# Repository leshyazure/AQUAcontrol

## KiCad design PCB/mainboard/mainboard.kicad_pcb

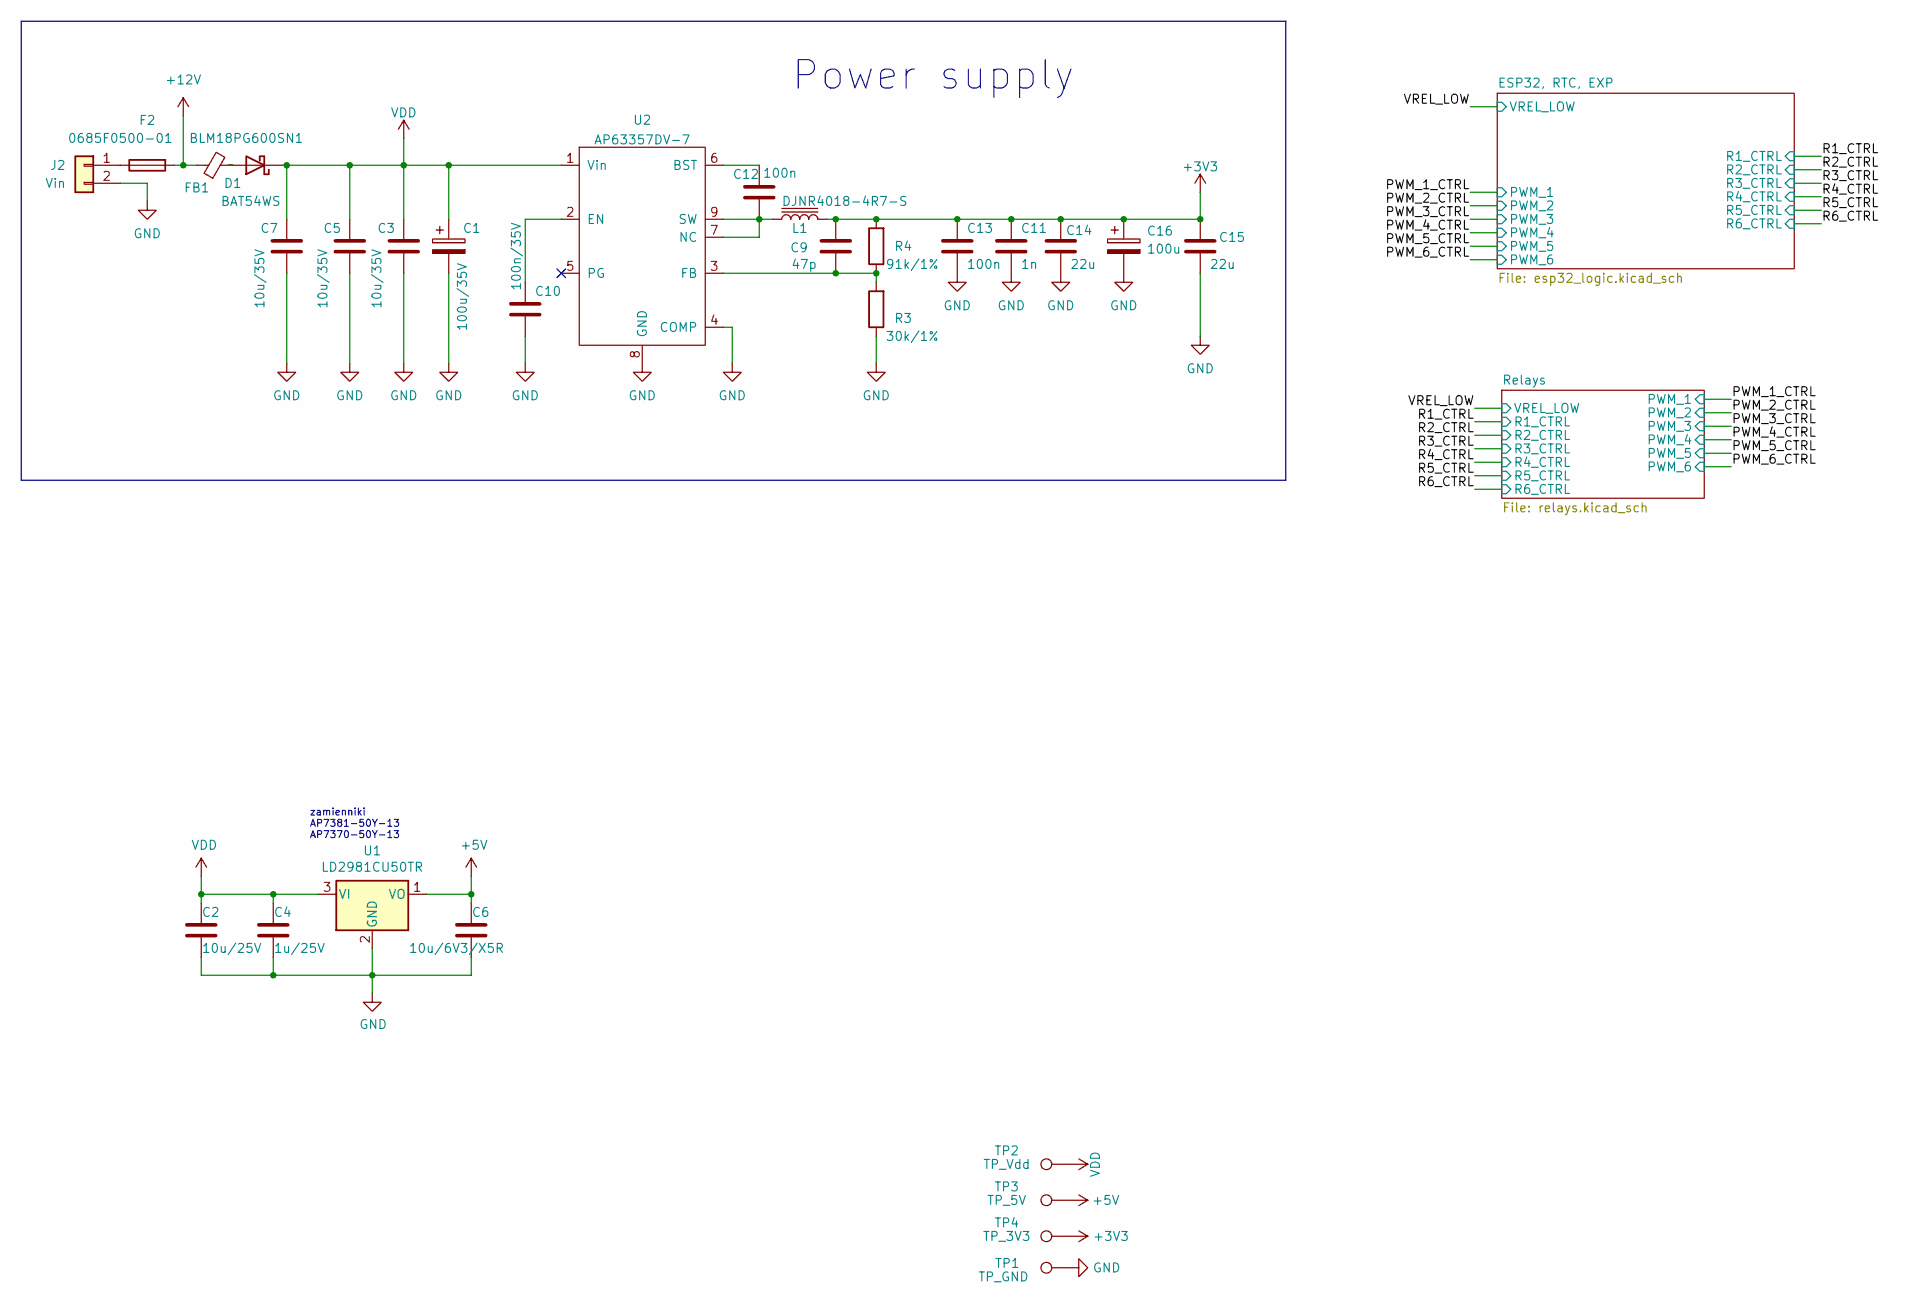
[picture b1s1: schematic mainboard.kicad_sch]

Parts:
C1: 100u/35V; CP_Elec_6.3x5.4
C2: 10u/25V; C_0805_2012Metric
C3, C5, C7: 10u/35V; C_1206_3216Metric
C4: 1u/25V; C_0603_1608Metric
C6: 10u/6V3/X5R; C_0603_1608Metric
C9: 47p; C_0603_1608Metric
C10: 100n/35V; C_0603_1608Metric
C11: 1n; C_0603_1608Metric
C12, C13: 100n; C_0603_1608Metric
C14, C15: 22u; C_0805_2012Metric
C16: 100u; CP_Elec_6.3x5.4
D1: BAT54WS; SOT-23
F2: 0685F0500-01; Fuse_1206_3216Metric
FB1: BLM18PG600SN1; L_0603_1608Metric
J2: Vin; PhoenixContact_MSTBA_2,5_2-G-5,08_1x02_P5.08mm_Horizontal
L1: DJNR4018-4R7-S; L_Bourns-SRN4018
R3: 30k/1%; R_0603_1608Metric_Pad0.98x0.95mm_HandSolder
R4: 91k/1%; R_0603_1608Metric_Pad0.98x0.95mm_HandSolder
TP1: TP_GND; TestPoint_THTPad_D1.0mm_Drill0.5mm
TP2: TP_Vdd; TestPoint_THTPad_D1.0mm_Drill0.5mm
TP3: TP_5V; TestPoint_THTPad_D1.0mm_Drill0.5mm
TP4: TP_3V3; TestPoint_THTPad_D1.0mm_Drill0.5mm
U1: LD2981CU50TR; SOT-89-3
U2: AP63357DV-7; V-DFN3020-13_Type_A_grid_stencil

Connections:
+3V3: C9.1, C11.1, C13.1, C14.1, C15.1, C16.1, L1.2, R4.2, TP4.1; also elsewhere on the board
+5V: C6.1, TP3.1, U1.1 (VO); also elsewhere on the board
+12V: F2.2, FB1.1; also elsewhere on the board
GND: C1.2, C2.2, C3.2, C4.2, C5.2, C6.2, C7.2, C10.2, C11.2, C13.2, C14.2, C15.2, C16.2, J2.2, R3.1, TP1.1, U1.2 (GND), U2.4 (COMP), U2.8 (GND); also elsewhere on the board
unnamed: C9.2, R3.2, R4.1, U2.3 (FB)
unnamed: C10.1, U2.2 (EN)
unnamed: C12.1, U2.6 (BST)
unnamed: C12.2, L1.1, U2.7 (NC), U2.9 (SW)
unnamed: D1.2 (A), FB1.2
unnamed: F2.1, J2.1
VDD: C1.1, C2.1, C3.1, C4.1, C5.1, C7.1, D1.1 (K), TP2.1, U1.3 (VI), U2.1 (Vin); also elsewhere on the board

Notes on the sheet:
zamienniki AP7381-50Y-13 AP7370-50Y-13
Power supply

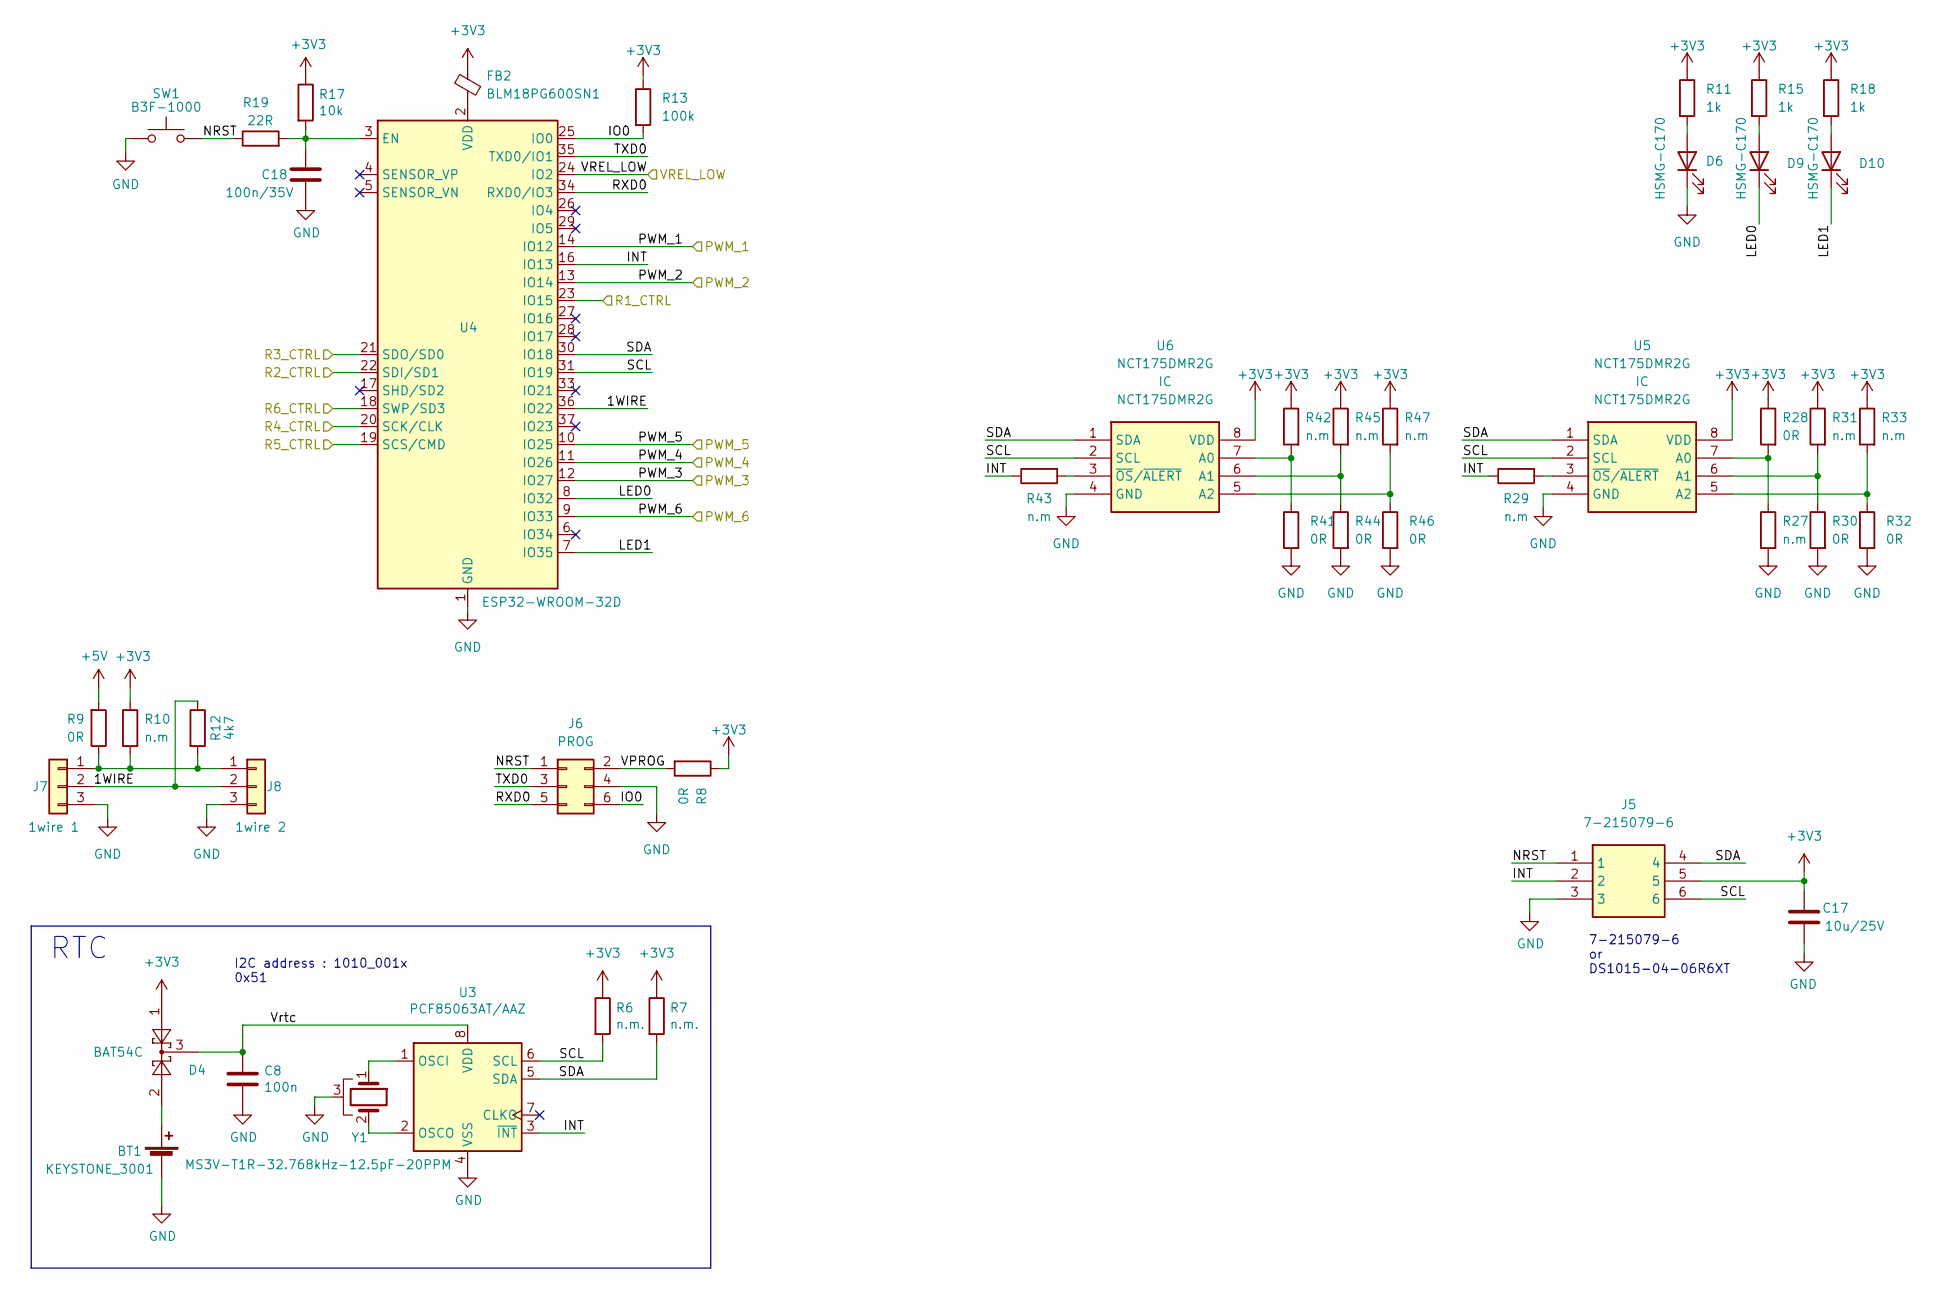
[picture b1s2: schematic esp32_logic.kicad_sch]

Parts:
BT1: KEYSTONE_3001; BatteryHolder_Keystone_3001_1x12mm
C8: 100n; C_0603_1608Metric_Pad1.08x0.95mm_HandSolder
C17: 10u/25V; C_1206_3216Metric_Pad1.33x1.80mm_HandSolder
C18: 100n/35V; C_0603_1608Metric_Pad1.08x0.95mm_HandSolder
D4: BAT54C; SOT-23
D6, D9, D10: HSMG-C170; LED_0805_2012Metric_Pad1.15x1.40mm_HandSolder
FB2: BLM18PG600SN1; L_0603_1608Metric
J5: 7-215079-6; Mouser Part Number 571-72150796
J6: PROG; PinHeader_2x03_P1.27mm_Vertical
J7: 1wire 1; JST_PH_B3B-PH-K_1x03_P2.00mm_Vertical
J8: 1wire 2; JST_PH_B3B-PH-K_1x03_P2.00mm_Vertical
R6, R7: n.m.; R_0603_1608Metric_Pad0.98x0.95mm_HandSolder
R8, R9: 0R; R_0603_1608Metric_Pad0.98x0.95mm_HandSolder
R10: n.m; R_0603_1608Metric_Pad0.98x0.95mm_HandSolder
R11, R15, R18: 1k; R_0603_1608Metric_Pad0.98x0.95mm_HandSolder
R12: 4k7; R_0603_1608Metric_Pad0.98x0.95mm_HandSolder
R13: 100k; R_0603_1608Metric_Pad0.98x0.95mm_HandSolder
R17: 10k; R_0603_1608Metric_Pad0.98x0.95mm_HandSolder
R19: 22R; R_0603_1608Metric_Pad0.98x0.95mm_HandSolder
R27, R29, R31, R33, R42, R43, R45, R47: n.m; R_0402_1005Metric_Pad0.72x0.64mm_HandSolder
R28, R30, R32, R41, R44, R46: 0R; R_0402_1005Metric_Pad0.72x0.64mm_HandSolder
SW1: B3F-1000; PTS815SJM250SMTRLFS
U3: PCF85063AT/AAZ; SOIC-8_3.9x4.9mm_P1.27mm
U4: ESP32-WROOM-32D; ESP32-WROOM-32
U5, U6: NCT175DMR2G; SOP65P490X110-8N; Mouser Part Number 863-NCT175DMR2G
Y1: MS3V-T1R-32.768kHz-12.5pF-20PPM; Crystal_SMD_MicroCrystal_MS3V-T1R

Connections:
+3V3: C17.1, D4.1, FB2.2, J5.5, R6.1, R7.1, R8.1, R10.1, R11.1, R13.1, R15.1, R17.1, R18.1, R28.1, R31.1, R33.1, R42.1, R45.1, R47.1, U5.8 (VDD), U6.8 (VDD); also elsewhere on the board
+5V: R9.2; also elsewhere on the board
/ESP32, RTC, EXP/1WIRE: J7.2, J8.2, R12.1, U4.36 (IO22)
/ESP32, RTC, EXP/INT: J5.2, R29.1, R43.1, U3.3 (~INT), U4.16 (IO13)
/ESP32, RTC, EXP/IO0: J6.6, R13.2, U4.25 (IO0)
/ESP32, RTC, EXP/LED0: D9.1 (K), U4.8 (IO32)
/ESP32, RTC, EXP/LED1: D10.1 (K), U4.7 (IO35)
/ESP32, RTC, EXP/NRST: J5.1, J6.1, R19.1, SW1.3 (B), SW1.4 (B)
/ESP32, RTC, EXP/RXD0: J6.5, U4.34 (RXD0/IO3)
/ESP32, RTC, EXP/SCL: J5.6, R6.2, U3.6 (SCL), U4.31 (IO19), U5.2 (SCL), U6.2 (SCL)
/ESP32, RTC, EXP/SDA: J5.4, R7.2, U3.5 (SDA), U4.30 (IO18), U5.1 (SDA), U6.1 (SDA)
/ESP32, RTC, EXP/TXD0: J6.3, U4.35 (TXD0/IO1)
/ESP32, RTC, EXP/VPROG: J6.2, R8.2
/ESP32, RTC, EXP/Vrtc: C8.1, D4.3, U3.8 (VDD)
/PWM_1_CTRL: U4.14 (IO12); also elsewhere on the board
/PWM_2_CTRL: U4.13 (IO14); also elsewhere on the board
/PWM_3_CTRL: U4.12 (IO27); also elsewhere on the board
/PWM_4_CTRL: U4.11 (IO26); also elsewhere on the board
/PWM_5_CTRL: U4.10 (IO25); also elsewhere on the board
/PWM_6_CTRL: U4.9 (IO33); also elsewhere on the board
/R1_CTRL: U4.23 (IO15); also elsewhere on the board
/R2_CTRL: U4.22 (SDI/SD1); also elsewhere on the board
/R3_CTRL: U4.21 (SDO/SD0); also elsewhere on the board
/R4_CTRL: U4.20 (SCK/CLK); also elsewhere on the board
/R5_CTRL: U4.19 (SCS/CMD); also elsewhere on the board
/R6_CTRL: U4.18 (SWP/SD3); also elsewhere on the board
/VREL_LOW: U4.24 (IO2); also elsewhere on the board
GND: BT1.2 (-), C8.2, C17.2, C18.2, D6.1 (K), J5.3, J6.4, J7.3, J8.3, R27.2, R30.2, R32.2, R41.2, R44.2, R46.2, SW1.1 (A), SW1.2 (A), U3.4 (VSS), U4.1 (GND), U4.15 (GND), U4.38 (GND), U4.39 (GND), U5.4 (GND), U6.4 (GND), Y1.3; also elsewhere on the board
unnamed: BT1.1 (+), D4.2
unnamed: C18.1, R17.2, R19.2, U4.3 (EN)
unnamed: D6.2 (A), R11.2
unnamed: D9.2 (A), R15.2
unnamed: D10.2 (A), R18.2
unnamed: FB2.1, U4.2 (VDD)
unnamed: J7.1, J8.1, R9.1, R10.2, R12.2
unnamed: R27.1, R28.2, U5.7 (A0)
unnamed: R29.2, U5.3 (~OS/~ALERT)
unnamed: R30.1, R31.2, U5.6 (A1)
unnamed: R32.1, R33.2, U5.5 (A2)
unnamed: R41.1, R42.2, U6.7 (A0)
unnamed: R43.2, U6.3 (~OS/~ALERT)
unnamed: R44.1, R45.2, U6.6 (A1)
unnamed: R46.1, R47.2, U6.5 (A2)
unnamed: U3.1 (OSCI), Y1.1
unnamed: U3.2 (OSCO), Y1.2

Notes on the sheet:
RTC
I2C address : 1010_001x 0x51
7-215079-6 or DS1015-04-06R6XT

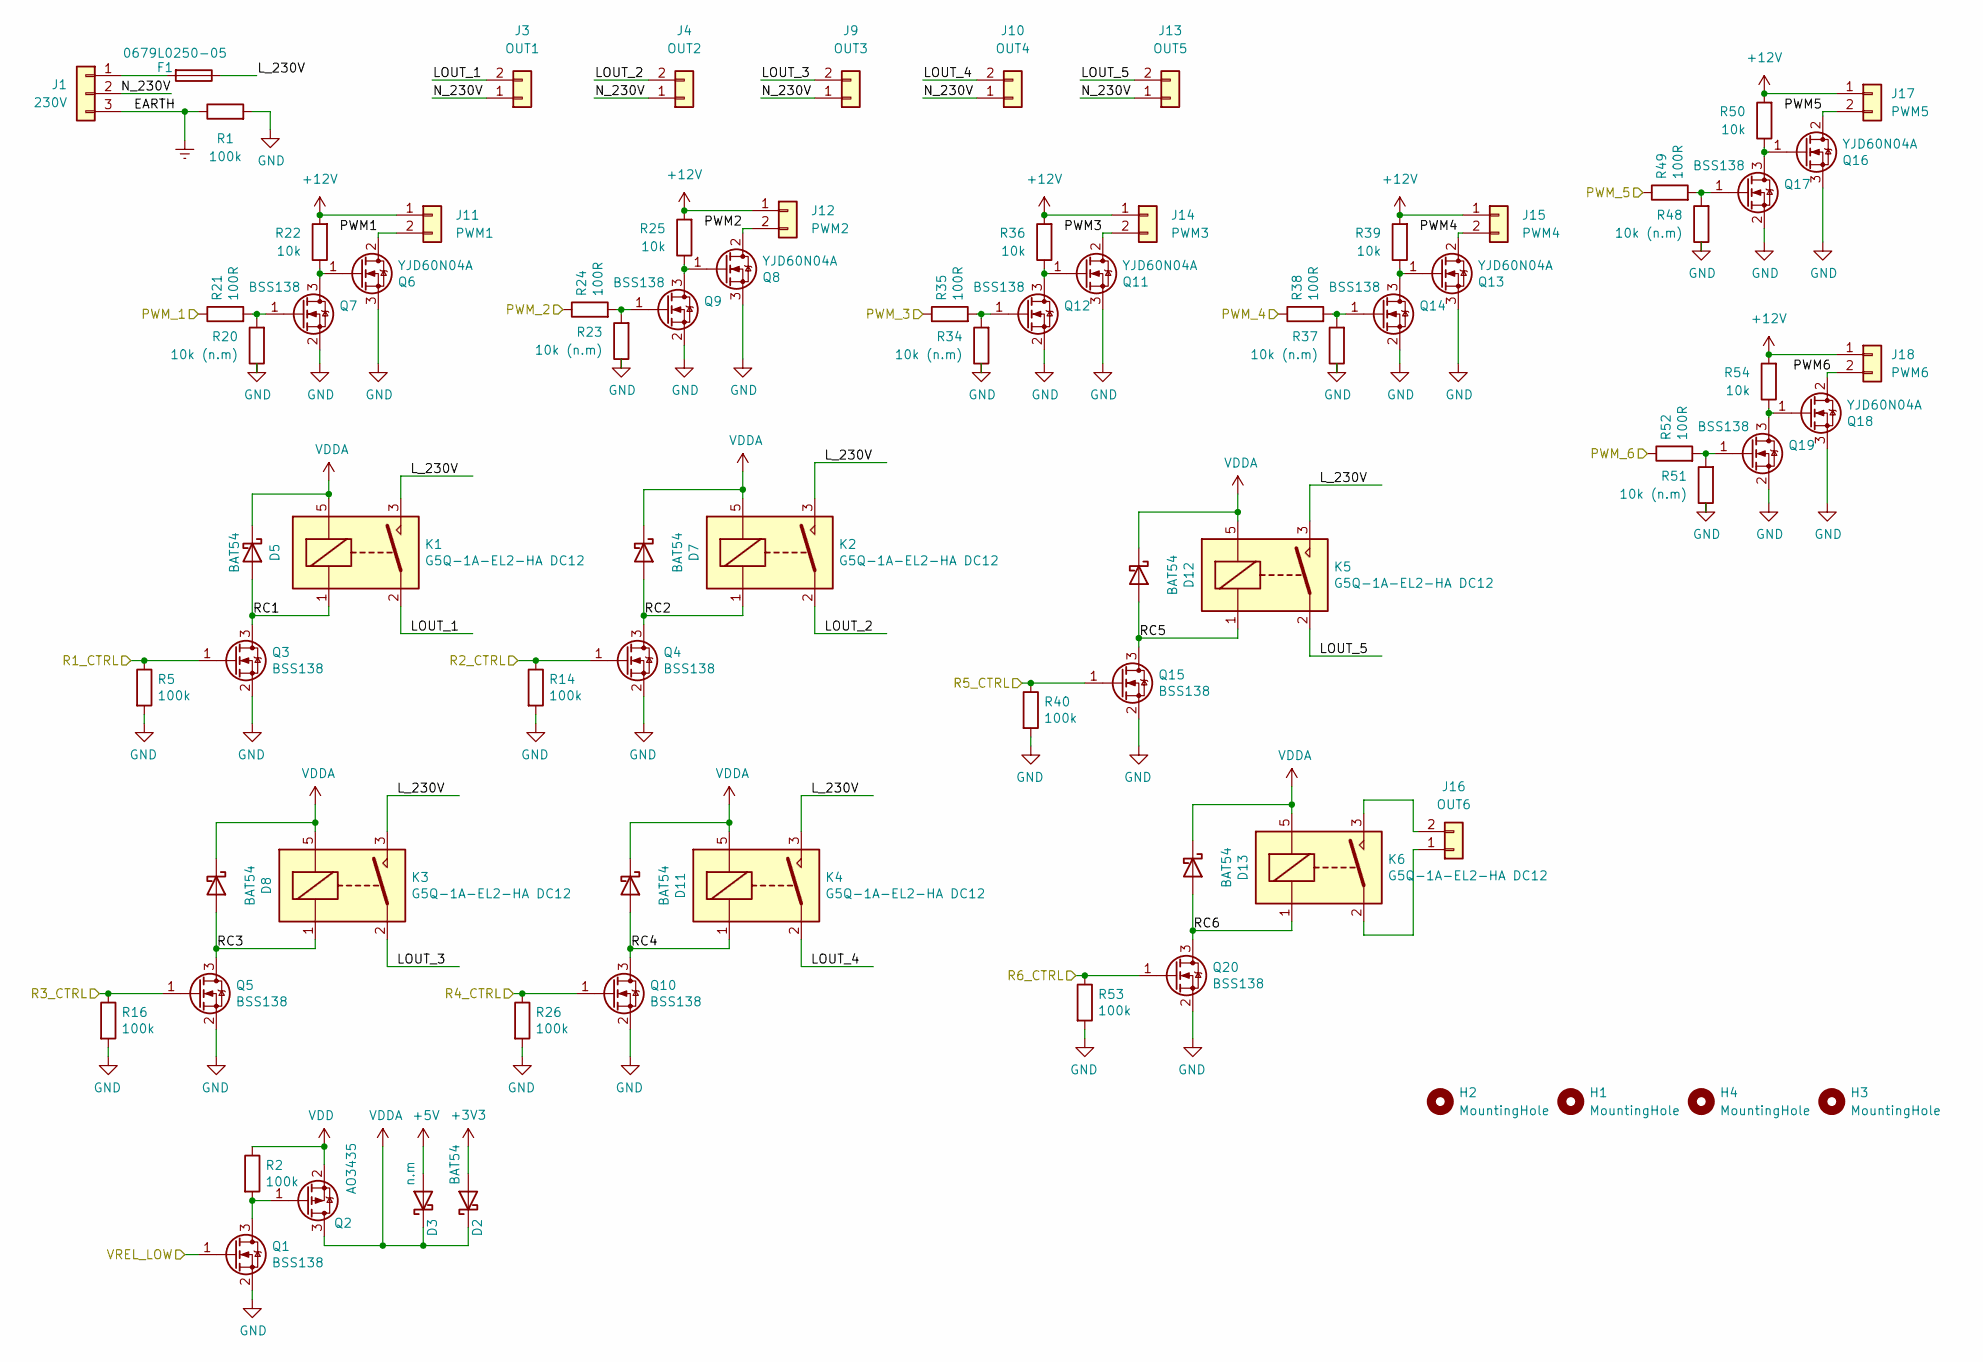
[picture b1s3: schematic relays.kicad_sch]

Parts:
D2, D5, D7, D8, D11, D12, D13: BAT54; SOT-23
D3: n.m; SOT-23
F1: 0679L0250-05; FUSC6125X279N
H1, H2, H3, H4: MountingHole; MountingHole_3.2mm_M3_Pad
J1: 230V; PhoenixContact_MSTBA_2,5_3-G-5,08_1x03_P5.08mm_Horizontal
J3: OUT1; PhoenixContact_MCV_1,5_2-G-3.5_1x02_P3.50mm_Vertical
J4: OUT2; PhoenixContact_MCV_1,5_2-G-3.5_1x02_P3.50mm_Vertical
J9: OUT3; PhoenixContact_MCV_1,5_2-G-3.5_1x02_P3.50mm_Vertical
J10: OUT4; PhoenixContact_MCV_1,5_2-G-3.5_1x02_P3.50mm_Vertical
J11: PWM1; JST_XH_B2B-XH-A_1x02_P2.50mm_Vertical
J12: PWM2; JST_XH_B2B-XH-A_1x02_P2.50mm_Vertical
J13: OUT5; PhoenixContact_MCV_1,5_2-G-3.5_1x02_P3.50mm_Vertical
J14: PWM3; JST_XH_B2B-XH-A_1x02_P2.50mm_Vertical
J15: PWM4; JST_XH_B2B-XH-A_1x02_P2.50mm_Vertical
J16: OUT6; PhoenixContact_MCV_1,5_2-G-3.5_1x02_P3.50mm_Vertical
J17: PWM5; JST_XH_B2B-XH-A_1x02_P2.50mm_Vertical
J18: PWM6; JST_XH_B2B-XH-A_1x02_P2.50mm_Vertical
K1, K2, K3, K4, K5, K6: G5Q-1A-EL2-HA DC12; Relay_SPST_Omron-G5Q-1A-sst_pf
Q1, Q3, Q4, Q5, Q7, Q9, Q10, Q12, Q14, Q15, Q17, Q19, Q20: BSS138; SOT-23
Q2: AO3435; SOT-23
Q6, Q8, Q11, Q13, Q16, Q18: YJD60N04A; TO-252-2
R1, R2, R5, R14, R16, R26, R40, R53: 100k; R_0603_1608Metric_Pad0.98x0.95mm_HandSolder
R20, R23, R34, R37, R48, R51: 10k (n.m); R_0603_1608Metric_Pad0.98x0.95mm_HandSolder
R21, R24, R35, R38, R49, R52: 100R; R_0603_1608Metric_Pad0.98x0.95mm_HandSolder
R22, R25, R36, R39, R50, R54: 10k; R_0603_1608Metric_Pad0.98x0.95mm_HandSolder

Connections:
+3V3: D2.1 (A); also elsewhere on the board
+5V: D3.1 (A); also elsewhere on the board
+12V: J11.1, J12.1, J14.1, J15.1, J17.1, J18.1, R22.2, R25.2, R36.2, R39.2, R50.2, R54.2; also elsewhere on the board
/PWM_1_CTRL: R21.1; also elsewhere on the board
/PWM_2_CTRL: R24.1; also elsewhere on the board
/PWM_3_CTRL: R35.1; also elsewhere on the board
/PWM_4_CTRL: R38.1; also elsewhere on the board
/PWM_5_CTRL: R49.1; also elsewhere on the board
/PWM_6_CTRL: R52.1; also elsewhere on the board
/R1_CTRL: Q3.1 (G), R5.1; also elsewhere on the board
/R2_CTRL: Q4.1 (G), R14.1; also elsewhere on the board
/R3_CTRL: Q5.1 (G), R16.1; also elsewhere on the board
/R4_CTRL: Q10.1 (G), R26.1; also elsewhere on the board
/R5_CTRL: Q15.1 (G), R40.1; also elsewhere on the board
/R6_CTRL: Q20.1 (G), R53.1; also elsewhere on the board
/Relays/LOUT_1: J3.2, K1.2
/Relays/LOUT_2: J4.2, K2.2
/Relays/LOUT_3: J9.2, K3.2
/Relays/LOUT_4: J10.2, K4.2
/Relays/LOUT_5: J13.2, K5.2
/Relays/L_230V: F1.1, K1.3, K2.3, K3.3, K4.3, K5.3
/Relays/N_230V: J1.2, J3.1, J4.1, J9.1, J10.1, J13.1
/Relays/PWM1: J11.2, Q6.2 (D)
/Relays/PWM2: J12.2, Q8.2 (D)
/Relays/PWM3: J14.2, Q11.2 (D)
/Relays/PWM4: J15.2, Q13.2 (D)
/Relays/PWM5: J17.2, Q16.2 (D)
/Relays/PWM6: J18.2, Q18.2 (D)
/Relays/RC1: D5.1 (A), K1.1, Q3.3 (D)
/Relays/RC2: D7.1 (A), K2.1, Q4.3 (D)
/Relays/RC3: D8.1 (A), K3.1, Q5.3 (D)
/Relays/RC4: D11.1 (A), K4.1, Q10.3 (D)
/Relays/RC5: D12.1 (A), K5.1, Q15.3 (D)
/Relays/RC6: D13.1 (A), K6.1, Q20.3 (D)
/VREL_LOW: Q1.1 (G); also elsewhere on the board
Earth: J1.3, R1.1
GND: Q1.2 (S), Q3.2 (S), Q4.2 (S), Q5.2 (S), Q6.3 (S), Q7.2 (S), Q8.3 (S), Q9.2 (S), Q10.2 (S), Q11.3 (S), Q12.2 (S), Q13.3 (S), Q14.2 (S), Q15.2 (S), Q16.3 (S), Q17.2 (S), Q18.3 (S), Q19.2 (S), Q20.2 (S), R1.2, R5.2, R14.2, R16.2, R20.1, R23.1, R26.2, R34.1, R37.1, R40.2, R48.1, R51.1, R53.2; also elsewhere on the board
unnamed: F1.2, J1.1
unnamed: J16.1, K6.2
unnamed: J16.2, K6.3
unnamed: Q1.3 (D), Q2.1 (G), R2.2
unnamed: Q6.1 (G), Q7.3 (D), R22.1
unnamed: Q7.1 (G), R20.2, R21.2
unnamed: Q8.1 (G), Q9.3 (D), R25.1
unnamed: Q9.1 (G), R23.2, R24.2
unnamed: Q11.1 (G), Q12.3 (D), R36.1
unnamed: Q12.1 (G), R34.2, R35.2
unnamed: Q13.1 (G), Q14.3 (D), R39.1
unnamed: Q14.1 (G), R37.2, R38.2
unnamed: Q16.1 (G), Q17.3 (D), R50.1
unnamed: Q17.1 (G), R48.2, R49.2
unnamed: Q18.1 (G), Q19.3 (D), R54.1
unnamed: Q19.1 (G), R51.2, R52.2
VDD: Q2.2 (S), R2.1; also elsewhere on the board
VDDA: D2.3 (K), D3.3 (K), D5.3 (K), D7.3 (K), D8.3 (K), D11.3 (K), D12.3 (K), D13.3 (K), K1.5, K2.5, K3.5, K4.5, K5.5, K6.5, Q2.3 (D)

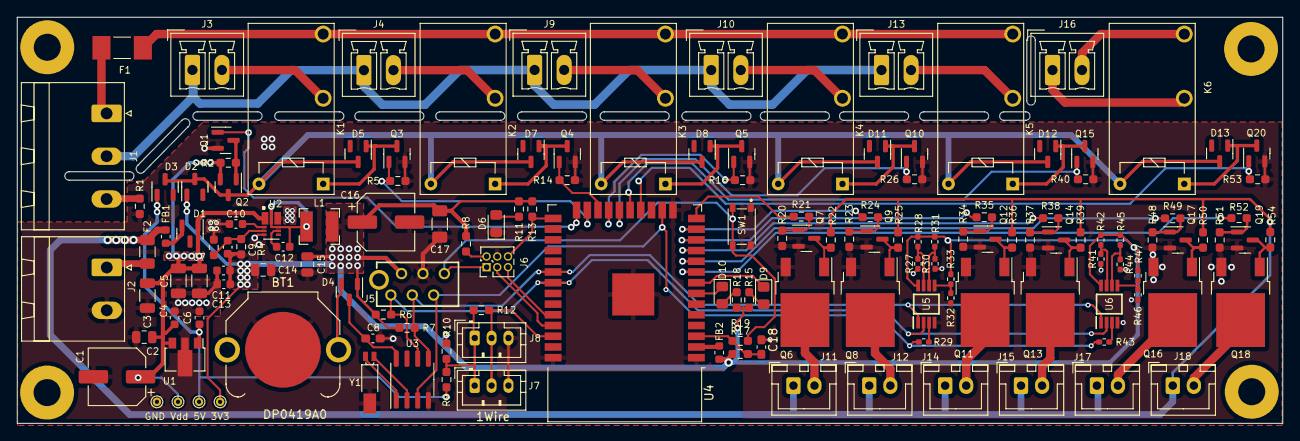
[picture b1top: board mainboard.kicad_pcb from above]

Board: 2 copper layers, 150.1 x 48.2 mm, 151 parts (0 on the bottom side), 90 nets.

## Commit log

2023-04-26 added rev0 mainboard PCB
